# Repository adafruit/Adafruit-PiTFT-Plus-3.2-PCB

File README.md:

## Adafruit PiTFT Plus 320x240 3.2" TFT + Resistive Touchscreen PCB
<a href="http://www.adafruit.com/products/2616"><br/>
Click here to purchase one from the Adafruit shop</a>

Is this not the cutest little display for the Raspberry Pi? It features a 3.2" display with 320x240 16-bit color pixels and a resistive touch overlay. The plate uses the high speed SPI interface on the Pi and can use the mini display as a console, X window port, displaying images or video etc. Best of all it plugs right in on top!

This design fits perfectly onto the Pi Zero, Pi 3, Pi 2 or Model A+, B+! (Any Pi with a 2x20 connector) Not for use with an old Pi 1 with 2x13 connector. This display is functionally the same as our classic PiTFT 2.8" and PiTFT Plus 2.8" - same pins used, same resolution, same drivers, but is just a bit bigger. It also has a 26- pins GPIO pins brought out so you can connect a 26-pin Raspberry Pi GPIO cable underneath. It's the same outline as a Pi 3 / 2 / B+ so it fits well on top of a Pi in our Raspberry Pi Enclosure base.

PCB files for the Adafruit PiTFT Plus 3.2" Display. The format is EagleCAD schematic and board layout
- https://www.adafruit.com/product/2616

### License

Adafruit invests time and resources providing this open source design, please support Adafruit and open-source hardware by purchasing products from [Adafruit](https://www.adafruit.com)!

All text above must be included in any redistribution

Designed by Limor Fried/Ladyada for Adafruit Industries.
Creative Commons Attribution/Share-Alike, all text above must be included in any redistribution. 
See license.txt for additional information.

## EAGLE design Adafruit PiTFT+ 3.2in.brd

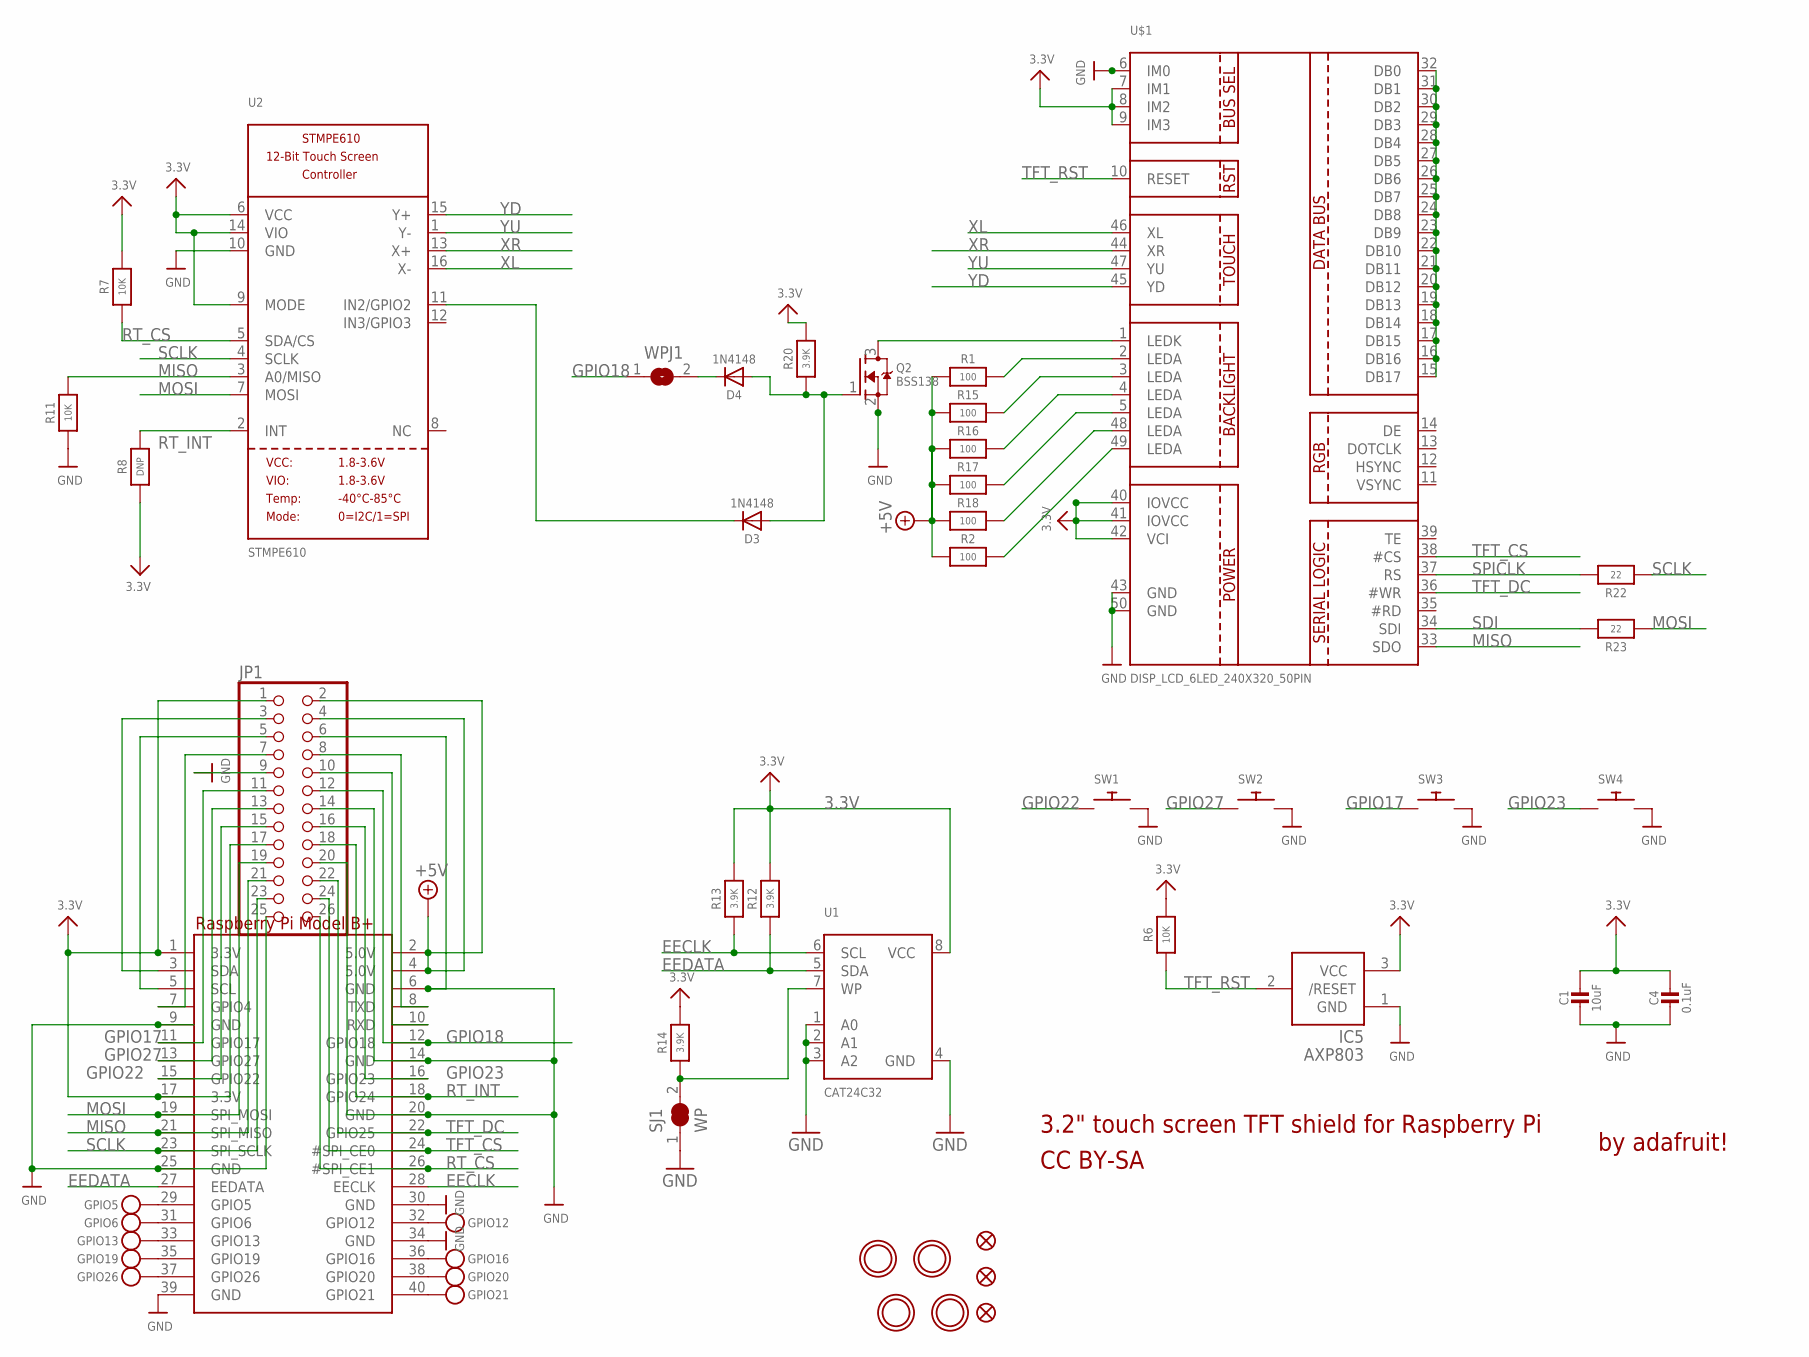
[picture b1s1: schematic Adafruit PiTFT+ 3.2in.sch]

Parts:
C1: 10uF; 0805-NO
C4: 0.1uF; 0805-NO
D3, D4: 1N4148; SOD-323
GPIO5, GPIO6, GPIO12, GPIO13, GPIO16, GPIO19, GPIO20, GPIO21, GPIO26: TESTPOINT1.5X2.0MM_NOCREAM; PAD-1.5X2.0
IC5: AXP803; SOT23
JP1: HEADER-2X13-SMT; 2X13_SMT_MALE
Q2: BSS138; SOT23-WIDE
R1, R2, R15, R16, R17, R18: 100; 0805-NO
R6, R7, R11: 10K; 0805-NO
R8: DNP; 0805-NO
R12, R13, R14, R20: 3.9K; 0805-NO
R22: 22; 0805-NO
R23: 22; _0805MP
RPI1: RASPBERRYPI_BPLUS_SMT; RASPBERRYPI_BPLUS_SHIELD_SMT
SJ1: WP; SOLDERJUMPER_CLOSEDWIRE
SW1, SW2, SW3, SW4: SWITCH_PUSHBUTTONEVQ-PE; TACT_PANA-EVQ
U1: CAT24C32; SOIC8_150MIL
U2: STMPE610; QFN16_3MM
U$1: DISP_LCD_6LED_240X320_50PIN; TFT_3.2IN_240X320_50PIN
U$10, U$11, U$18: FIDUCIAL""; FIDUCIAL_1MM
U$15, U$16, U$17, U$20: MOUNTINGHOLE2.5_THICK; MOUNTINGHOLE_2.5_PLATED_THICK
WPJ1: SOLDERJUMPERCLOSED; SOLDERJUMPER_CLOSEDWIRE

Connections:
3.3V: C1.1, C4.1, IC5.3 (VCC), JP1.1, JP1.17, R6.2, R7.2, R8.1, R12.2, R13.2, R14.2, R20.2, RPI1.1 (3.3V), RPI1.17 (3.3V), U1.8 (VCC), U2.6 (VCC), U2.9 (MODE), U2.14 (VIO), U$1.7 (IM1), U$1.8 (IM2), U$1.9 (IM3), U$1.40 (IOVCC), U$1.41 (IOVCC), U$1.42 (VCI)
+5V: JP1.2, JP1.4, R1.1, R2.1, R15.1, R16.1, R17.1, R18.1, RPI1.2 (5.0V), RPI1.4 (5.0V)
EECLK: R13.1, RPI1.28 (EECLK), U1.6 (SCL)
EEDATA: R12.1, RPI1.27 (EEDATA), U1.5 (SDA)
GND: C1.2, C4.2, IC5.1 (GND), JP1.6, JP1.9, JP1.14, JP1.20, JP1.25, Q2.2 (S), R11.1, RPI1.6 (GND), RPI1.9 (GND), RPI1.14 (GND), RPI1.20 (GND), RPI1.25 (GND), RPI1.30 (GND), RPI1.34 (GND), RPI1.39 (GND), SJ1.1, SW1.P$2, SW2.P$2, SW3.P$2, SW4.P$2, U1.1 (A0), U1.2 (A1), U1.3 (A2), U1.4 (GND), U2.10 (GND), U$1.6 (IM0), U$1.43 (GND), U$1.50 (GND)
GPIO6: GPIO6.P$1, RPI1.31 (GPIO6)
GPIO16: GPIO16.P$1, RPI1.36 (GPIO16)
GPIO17: JP1.11, RPI1.11 (GPIO17), SW3.P$1
GPIO18: JP1.12, RPI1.12 (GPIO18), WPJ1.1
GPIO22: JP1.15, RPI1.15 (GPIO22), SW1.P$1
GPIO23: JP1.16, RPI1.16 (GPIO23), SW4.P$1
GPIO27: JP1.13, RPI1.13 (GPIO27), SW2.P$1
MISO: JP1.21, R11.2, RPI1.21 (SPI_MISO), U2.3 (A0/MISO), U$1.33 (SDO)
MOSI: JP1.19, R23.1, RPI1.19 (SPI_MOSI), U2.7 (MOSI)
unnamed: R2.2, U$1.49 (LEDA)
unnamed: R1.2, U$1.2 (LEDA)
unnamed: D3.C, U2.11 (IN2/GPIO2)
unnamed: GPIO5.P$1, RPI1.29 (GPIO5)
unnamed: JP1.3, RPI1.3 (SDA)
unnamed: JP1.5, RPI1.5 (SCL)
unnamed: JP1.7, RPI1.7 (GPIO4)
unnamed: GPIO13.P$1, RPI1.33 (GPIO13)
unnamed: GPIO19.P$1, RPI1.35 (GPIO19)
unnamed: GPIO26.P$1, RPI1.37 (GPIO26)
unnamed: GPIO12.P$1, RPI1.32 (GPIO12)
unnamed: GPIO20.P$1, RPI1.38 (GPIO20)
unnamed: R14.1, SJ1.2, U1.7 (WP)
unnamed: JP1.10, RPI1.10 (RXD)
unnamed: JP1.8, RPI1.8 (TXD)
unnamed: GPIO21.P$1, RPI1.40 (GPIO21)
unnamed: D3.A, D4.A, Q2.1 (G), R20.1
unnamed: U$1.15 (DB17), U$1.16 (DB16), U$1.17 (DB15), U$1.18 (DB14), U$1.19 (DB13), U$1.20 (DB12), U$1.21 (DB11), U$1.22 (DB10), U$1.23 (DB9), U$1.24 (DB8), U$1.25 (DB7), U$1.26 (DB6), U$1.27 (DB5), U$1.28 (DB4), U$1.29 (DB3), U$1.30 (DB2), U$1.31 (DB1), U$1.32 (DB0)
unnamed: Q2.3 (D), U$1.1 (LEDK)
unnamed: R15.2, U$1.3 (LEDA)
unnamed: R16.2, U$1.4 (LEDA)
unnamed: R17.2, U$1.5 (LEDA)
unnamed: R18.2, U$1.48 (LEDA)
unnamed: D4.C, WPJ1.2
RT_CS: JP1.26, R7.1, RPI1.26 (#SPI_CE1), U2.5 (SDA/CS)
RT_INT: JP1.18, R8.2, RPI1.18 (GPIO24), U2.2 (INT)
SCLK: JP1.23, R22.1, RPI1.23 (SPI_SCLK), U2.4 (SCLK)
SDI: R23.2, U$1.34 (SDI)
SPICLK: R22.2, U$1.37 (RS)
TFT_CS: JP1.24, RPI1.24 (#SPI_CE0), U$1.38 (#CS)
TFT_DC: JP1.22, RPI1.22 (GPIO25), U$1.36 (#WR)
TFT_RST: IC5.2 (/RESET), R6.1, U$1.10 (RESET)
XL: U2.16 (X-), U$1.46 (XL)
XR: U2.13 (X+), U$1.44 (XR)
YD: U2.15 (Y+), U$1.45 (YD)
YU: U2.1 (Y-), U$1.47 (YU)

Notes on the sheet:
3.2" touch screen TFT shield for Raspberry Pi
by adafruit!
CC BY-SA

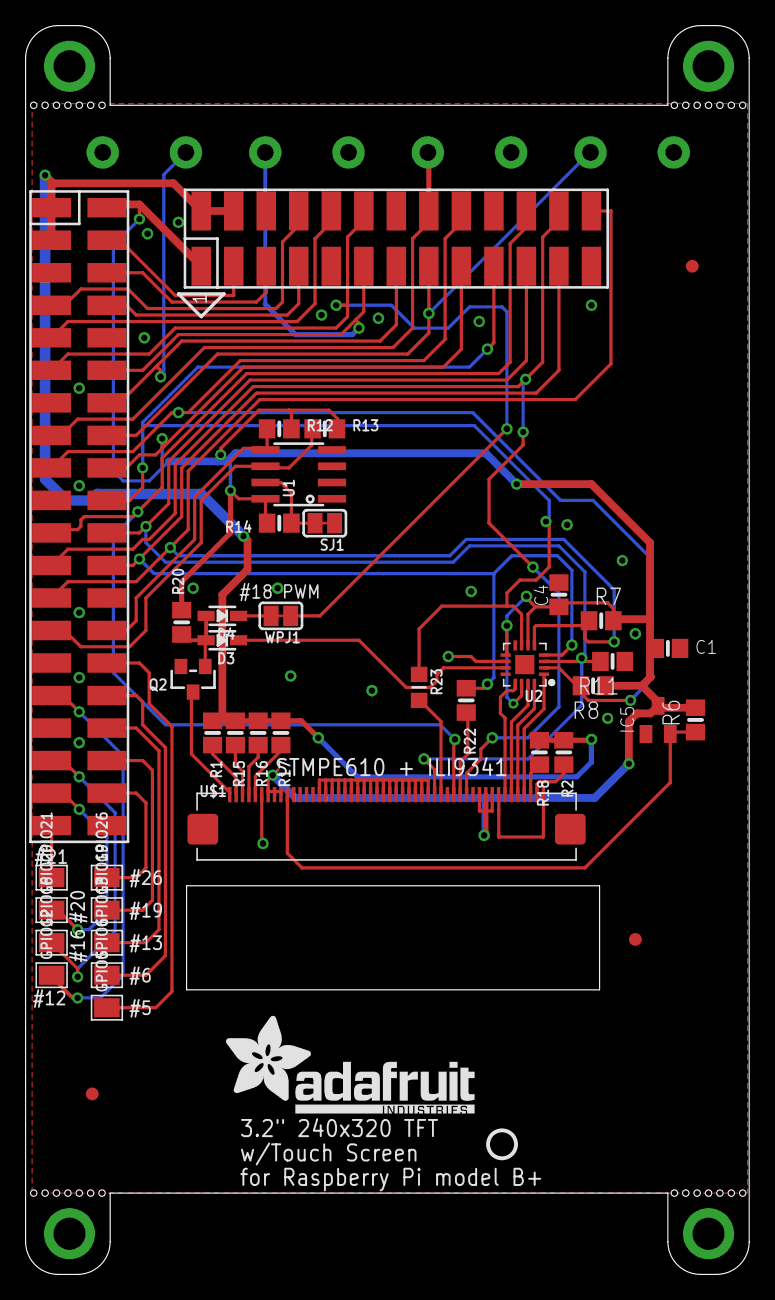
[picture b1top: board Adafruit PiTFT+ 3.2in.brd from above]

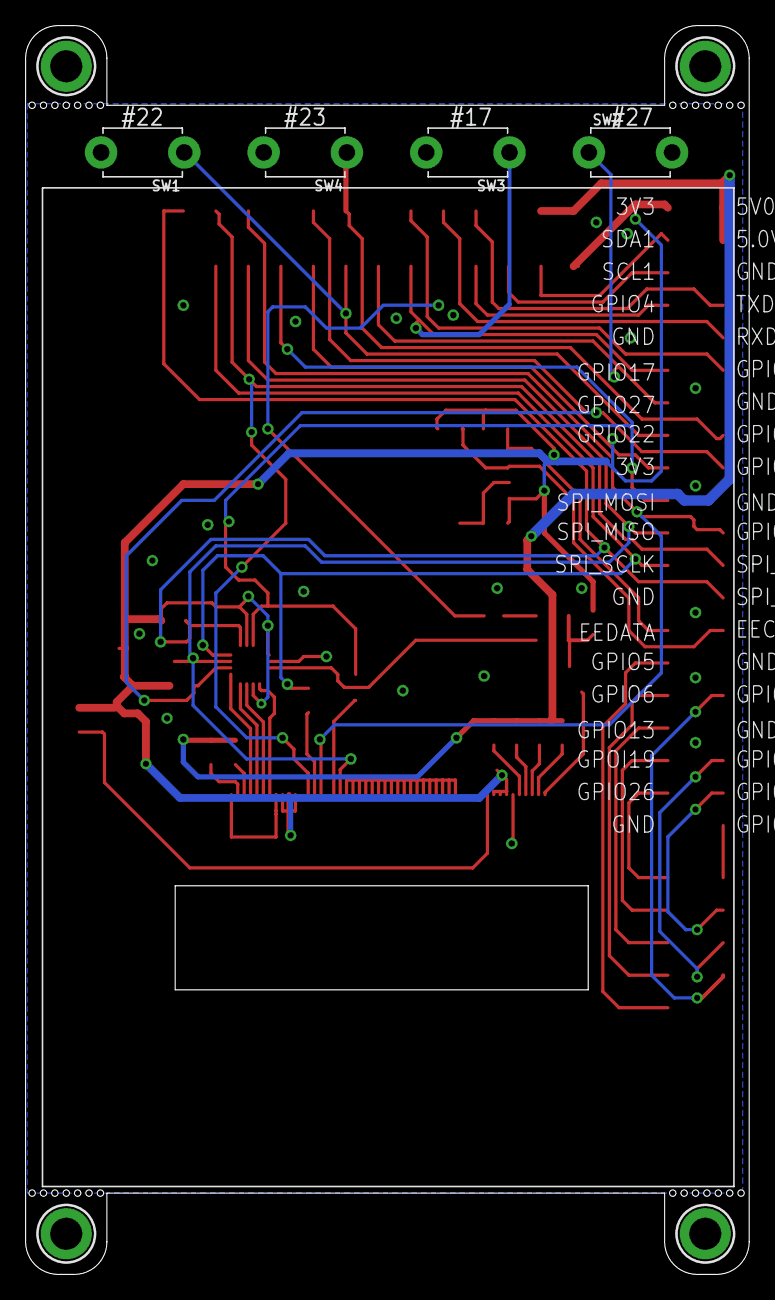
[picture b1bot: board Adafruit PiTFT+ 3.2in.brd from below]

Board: 2 copper layers, 56.5 x 97.5 mm, 51 parts (10 on the bottom side), 50 nets.

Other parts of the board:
U$19: PCBFEAT-REV-056
U$23: ADAFRUIT_TEXT_20MM

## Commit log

2016-06-27 init
